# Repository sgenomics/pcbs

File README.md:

# pcbs

There are my personal PCBs... contact me for licensing information.

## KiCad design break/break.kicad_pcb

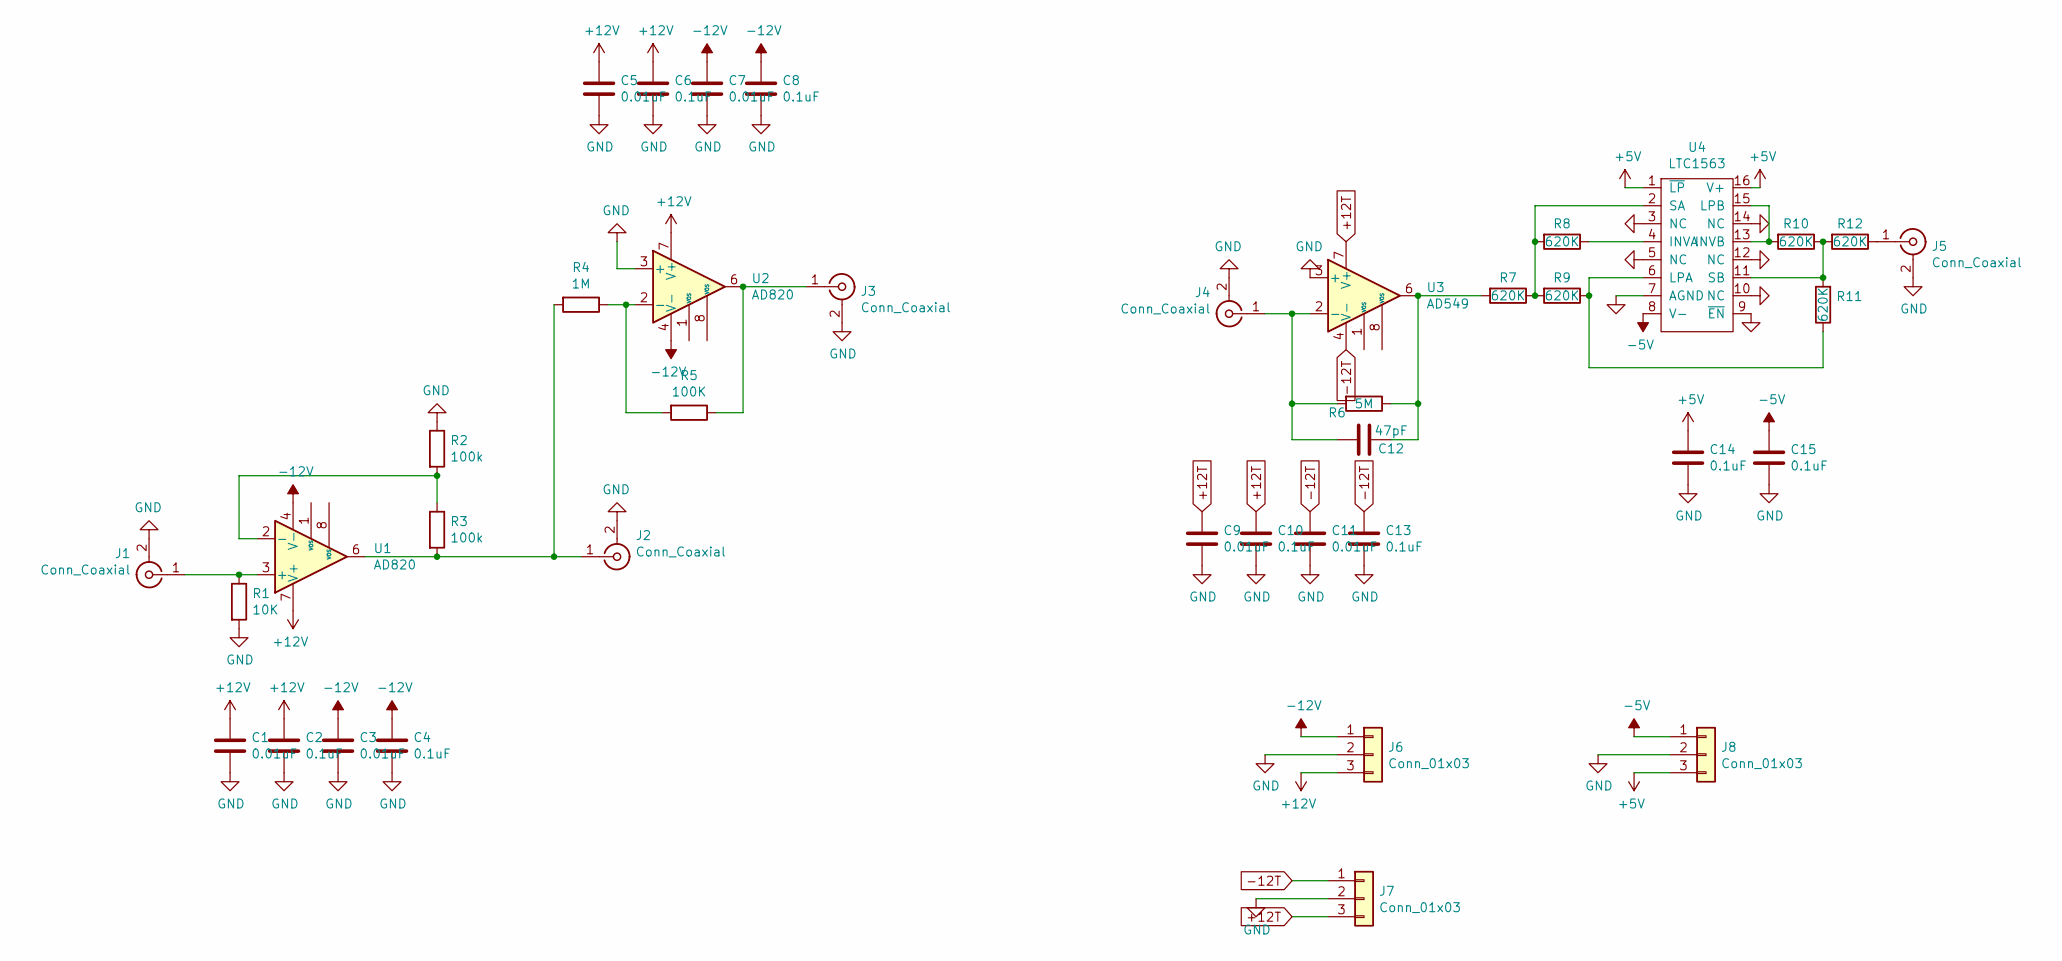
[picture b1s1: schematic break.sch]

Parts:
C1, C3, C5, C7, C9, C11: 0.01uF; C_0805_2012Metric
C2, C4, C6, C8, C10, C13, C14, C15: 0.1uF; C_0805_2012Metric
C12: 47pF; C_0805_2012Metric
J1, J2, J3, J4, J5: Conn_Coaxial; SMA_Amphenol_901-144_Vertical
J6, J7, J8: Conn_01x03; JST_EH_B3B-EH-A_1x03_P2.50mm_Vertical
R1: 10K; R_1206_3216Metric
R2, R3: 100k; R_1206_3216Metric
R4: 1M; R_1206_3216Metric
R5: 100K; R_1206_3216Metric
R6: 5M; R_1206_3216Metric
R7, R8, R9, R10, R11, R12: 620K; R_1206_3216Metric
U1, U2: AD820; SOIC-8_3.9x4.9mm_P1.27mm
U3: AD549; TO-99-8
U4: LTC1563; SSOP-16_3.9x4.9mm_P0.635mm

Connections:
+5V: C14.1, J8.3, U4.1 (~LP), U4.16 (V+)
+12T: C9.1, C10.1, J7.3, U3.7 (V+)
+12V: C1.1, C2.1, C5.1, C6.1, J6.3, U1.7 (V+), U2.7 (V+)
-5V: C15.1, J8.1, U4.8 (V-)
-12T: C11.1, C13.1, J7.1, U3.4 (V-)
-12V: C3.1, C4.1, C7.1, C8.1, J6.1, U1.4 (V-), U2.4 (V-)
GND: C1.2, C2.2, C3.2, C4.2, C5.2, C6.2, C7.2, C8.2, C9.2, C10.2, C11.2, C13.2, C14.2, C15.2, J1.2 (Ext), J2.2 (Ext), J3.2 (Ext), J4.2 (Ext), J5.2 (Ext), J6.2, J7.2, J8.2, R1.2, R2.1, U2.3 (+), U3.3 (+), U4.3 (NC), U4.5 (NC), U4.7 (AGND), U4.9 (~EN), U4.10 (NC), U4.12 (NC), U4.14 (NC)
unnamed: C12.1, R6.1, R7.2, U3.6
unnamed: C12.2, J4.1 (In), R6.2, U3.2 (-)
unnamed: J1.1 (In), R1.1, U1.3 (+)
unnamed: J2.1 (In), R3.2, R4.2, U1.6
unnamed: J3.1 (In), R5.1, U2.6
unnamed: J5.1 (In), R12.1
unnamed: R2.2, R3.1, U1.2 (-)
unnamed: R4.1, R5.2, U2.2 (-)
unnamed: R7.1, R8.2, R9.2, U4.2 (SA)
unnamed: R8.1, U4.4 (INVA)
unnamed: R10.1, R11.2, R12.2, U4.11 (SB)
unnamed: R10.2, U4.13 (INVB), U4.15 (LPB)
unnamed: R9.1, R11.1, U4.6 (LPA)

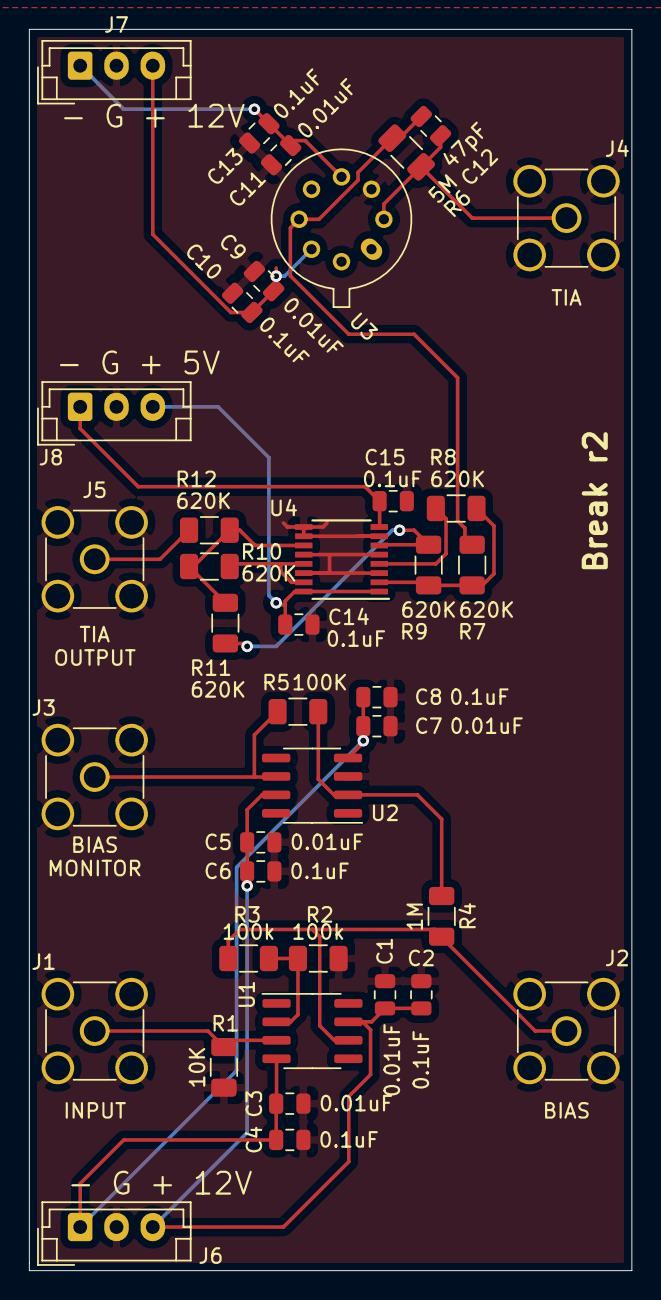
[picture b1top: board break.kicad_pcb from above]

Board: 2 copper layers, 41.5 x 85.5 mm, 39 parts (0 on the bottom side), 20 nets.

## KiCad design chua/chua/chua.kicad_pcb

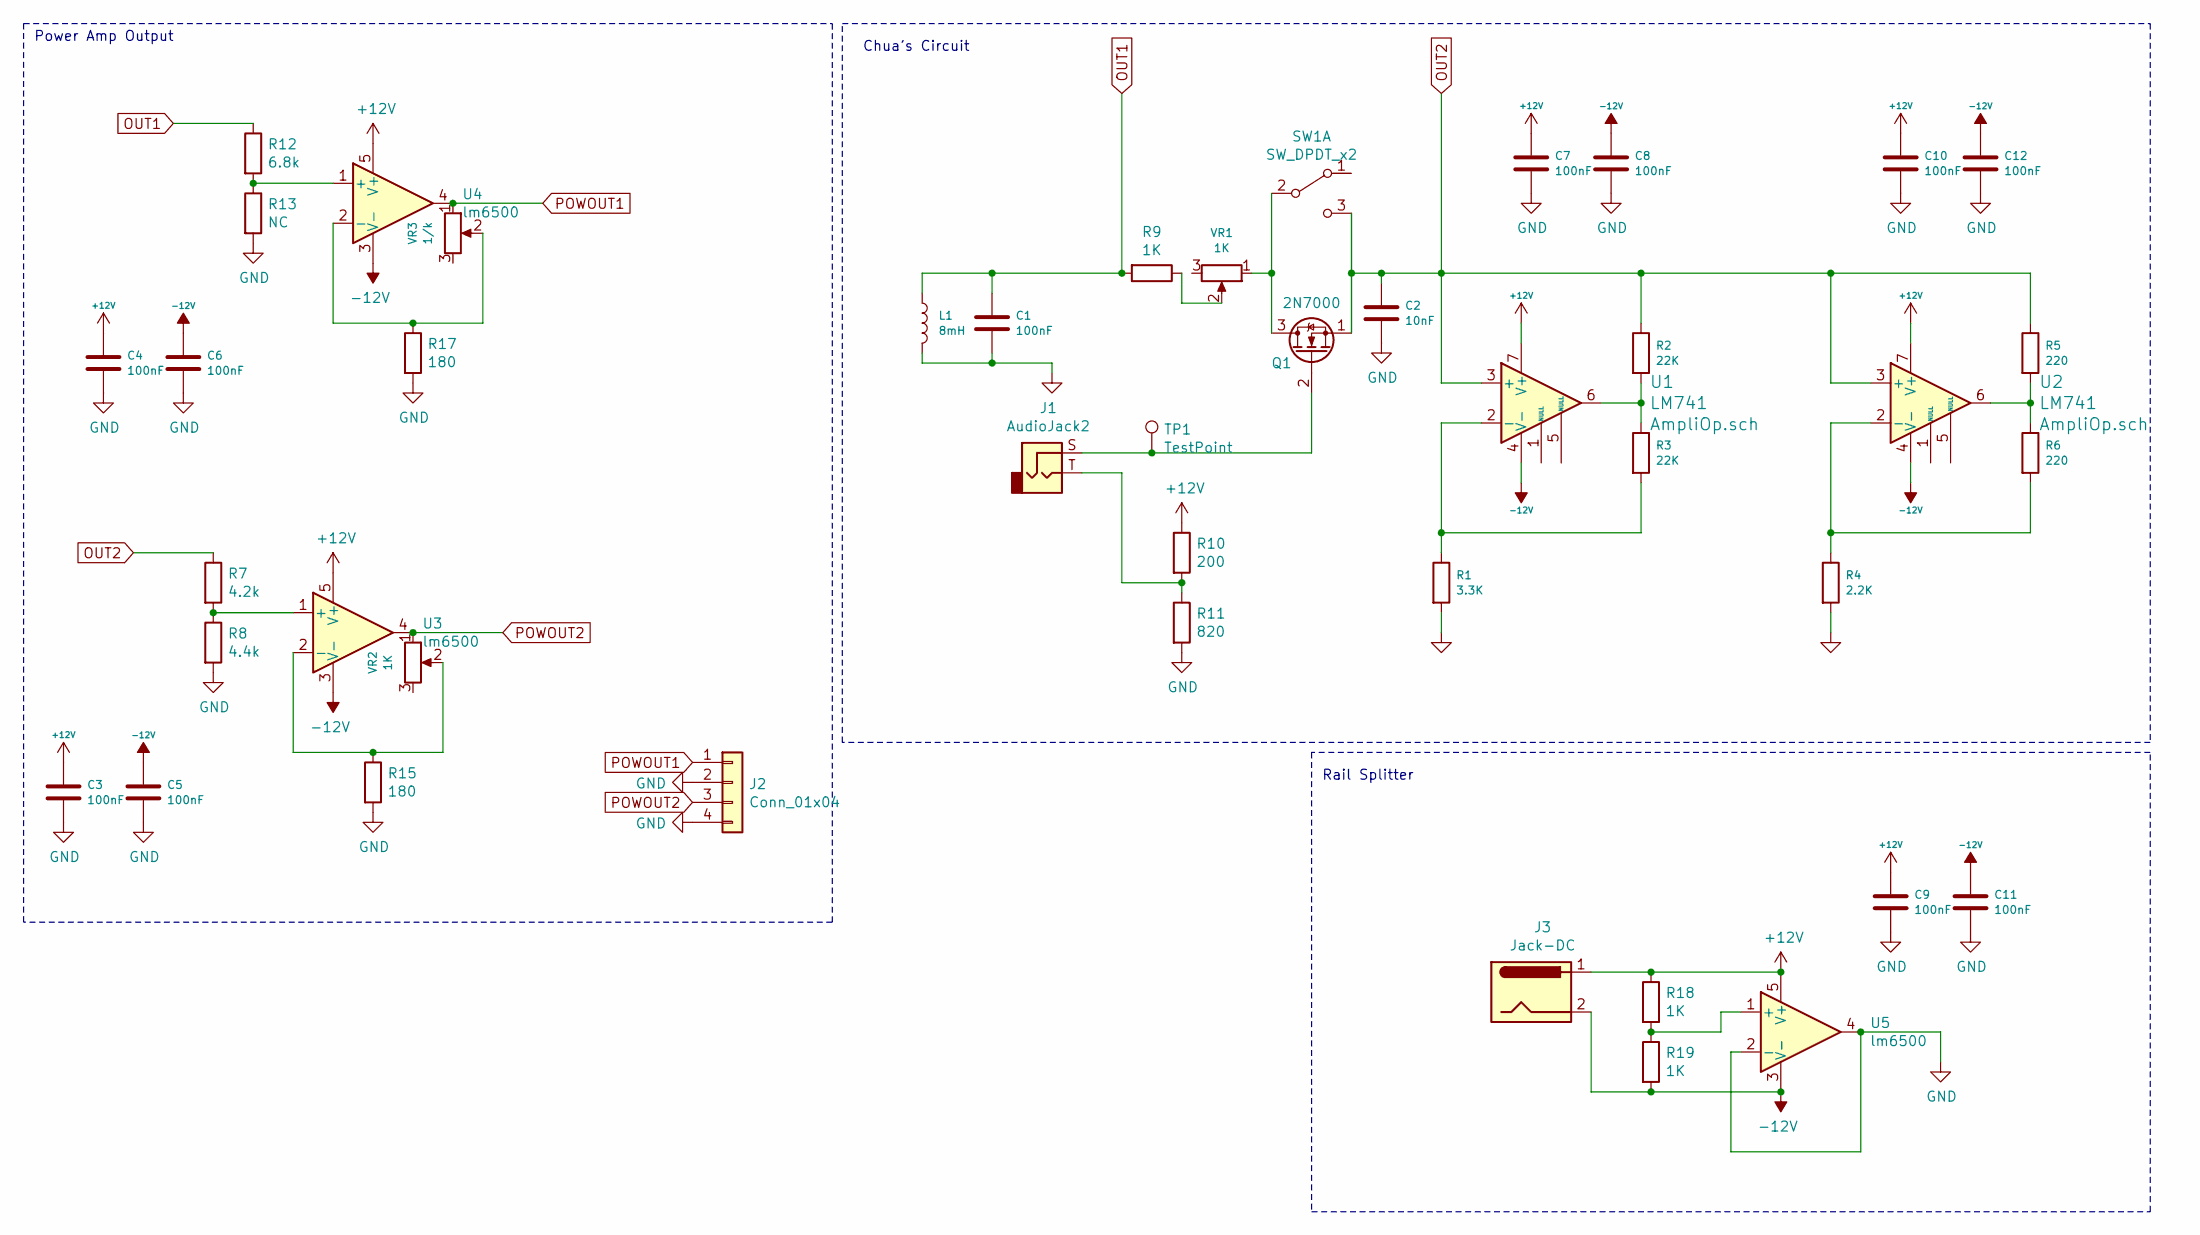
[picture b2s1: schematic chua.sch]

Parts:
C1: 100nF; C_Rect_L9.0mm_W2.5mm_P7.50mm_MKT
C2: 10nF; C_Rect_L10.0mm_W2.5mm_P7.50mm_MKS4
C3, C4, C5, C6, C7, C8, C9, C10, C11, C12: 100nF; C_Rect_L4.0mm_W2.5mm_P2.50mm
J1: AudioJack2; Banana_Jack_2Pin
J2: Conn_01x04; TerminalBlock_TE_282834-4_1x04_P2.54mm_Horizontal
J3: Jack-DC; BarrelJack_CUI_PJ-063AH_Horizontal
L1: 8mH; L_Radial_D8.7mm_P5.00mm_Fastron_07HCP
Q1: 2N7000; TO-92_Inline_Wide
R1: 3.3K; R_Axial_DIN0207_L6.3mm_D2.5mm_P10.16mm_Horizontal
R2, R3: 22K; R_Axial_DIN0207_L6.3mm_D2.5mm_P10.16mm_Horizontal
R4: 2.2K; R_Axial_DIN0207_L6.3mm_D2.5mm_P10.16mm_Horizontal
R5, R6: 220; R_Axial_DIN0207_L6.3mm_D2.5mm_P10.16mm_Horizontal
R7: 4.2k; R_Axial_DIN0207_L6.3mm_D2.5mm_P10.16mm_Horizontal
R8: 4.4k; R_Axial_DIN0207_L6.3mm_D2.5mm_P10.16mm_Horizontal
R9, R18, R19: 1K; R_Axial_DIN0207_L6.3mm_D2.5mm_P10.16mm_Horizontal
R10: 200; R_Axial_DIN0207_L6.3mm_D2.5mm_P10.16mm_Horizontal
R11: 820; R_Axial_DIN0207_L6.3mm_D2.5mm_P10.16mm_Horizontal
R12: 6.8k; R_Axial_DIN0207_L6.3mm_D2.5mm_P10.16mm_Horizontal
R13: NC; R_Axial_DIN0207_L6.3mm_D2.5mm_P10.16mm_Horizontal
R15, R17: 180; R_Axial_DIN0207_L6.3mm_D2.5mm_P10.16mm_Horizontal
SW1: SW_DPDT_x2; CK_FARN1201430
TP1: TestPoint; Test_Point_Pad_4.0x4.0mm
U1, U2: LM741; DIP-8_W7.62mm_LongPads
U3, U4, U5: lm6500; TO-220-5_P3.4x3.7mm_StaggerOdd_Lead3.8mm_Vertical
VR1, VR2: 1K; Potentiometer_WirePads_largePads
VR3: 1/k; Potentiometer_WirePads_largePads

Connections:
+12V: C3.1, C4.1, C7.1, C9.1, C10.1, J3.1, R10.1, R18.1, U1.7 (V+), U2.7 (V+), U3.5 (V+), U4.5 (V+), U5.5 (V+)
-12V: C5.1, C6.1, C8.1, C11.1, C12.1, J3.2, R19.2, U1.4 (V-), U2.4 (V-), U3.3 (V-), U4.3 (V-), U5.3 (V-)
GND: C1.2, C2.2, C3.2, C4.2, C5.2, C6.2, C7.2, C8.2, C9.2, C10.2, C11.2, C12.2, J2.2, J2.4, L1.2, R1.2, R4.2, R8.2, R11.2, R13.2, R15.2, R17.2, U5.2 (-), U5.4
unnamed: J1.S, Q1.2 (G), TP1.1
unnamed: J1.T, R10.2, R11.1
unnamed: Q1.3 (D), SW1.2 (B), VR1.1
unnamed: R1.1, R3.2, U1.2 (-)
unnamed: R2.2, R3.1, U1.6
unnamed: R4.1, R6.2, U2.2 (-)
unnamed: R5.2, R6.1, U2.6
unnamed: R7.2, R8.1, U3.1 (+)
unnamed: R9.1, VR1.2
unnamed: R12.2, R13.1, U4.1 (+)
unnamed: R15.1, U3.2 (-), VR2.2
unnamed: R17.1, U4.2 (-), VR3.2
unnamed: R18.2, R19.1, U5.1 (+)
OUT1: C1.1, L1.1, R9.2, R12.1
OUT2: C2.1, Q1.1 (S), R2.1, R5.1, R7.1, SW1.3 (C), U1.3 (+), U2.3 (+)
POWOUT1: J2.1, U4.4, VR3.1
POWOUT2: J2.3, U3.4, VR2.1

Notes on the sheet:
Chua’s Circuit
Power Amp Output
Rail Splitter

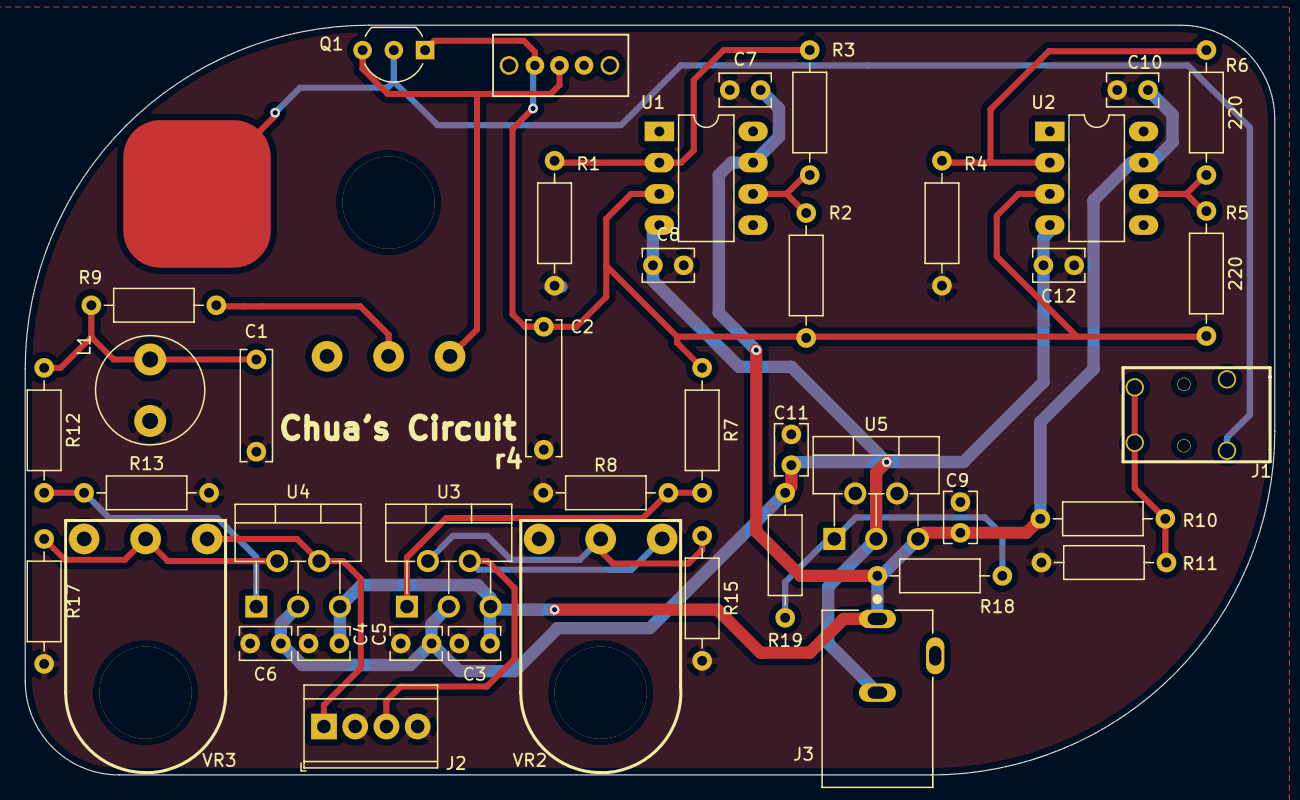
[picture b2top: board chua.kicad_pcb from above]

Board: 2 copper layers, 101.6 x 61.0 mm, 44 parts (1 on the bottom side), 20 nets.

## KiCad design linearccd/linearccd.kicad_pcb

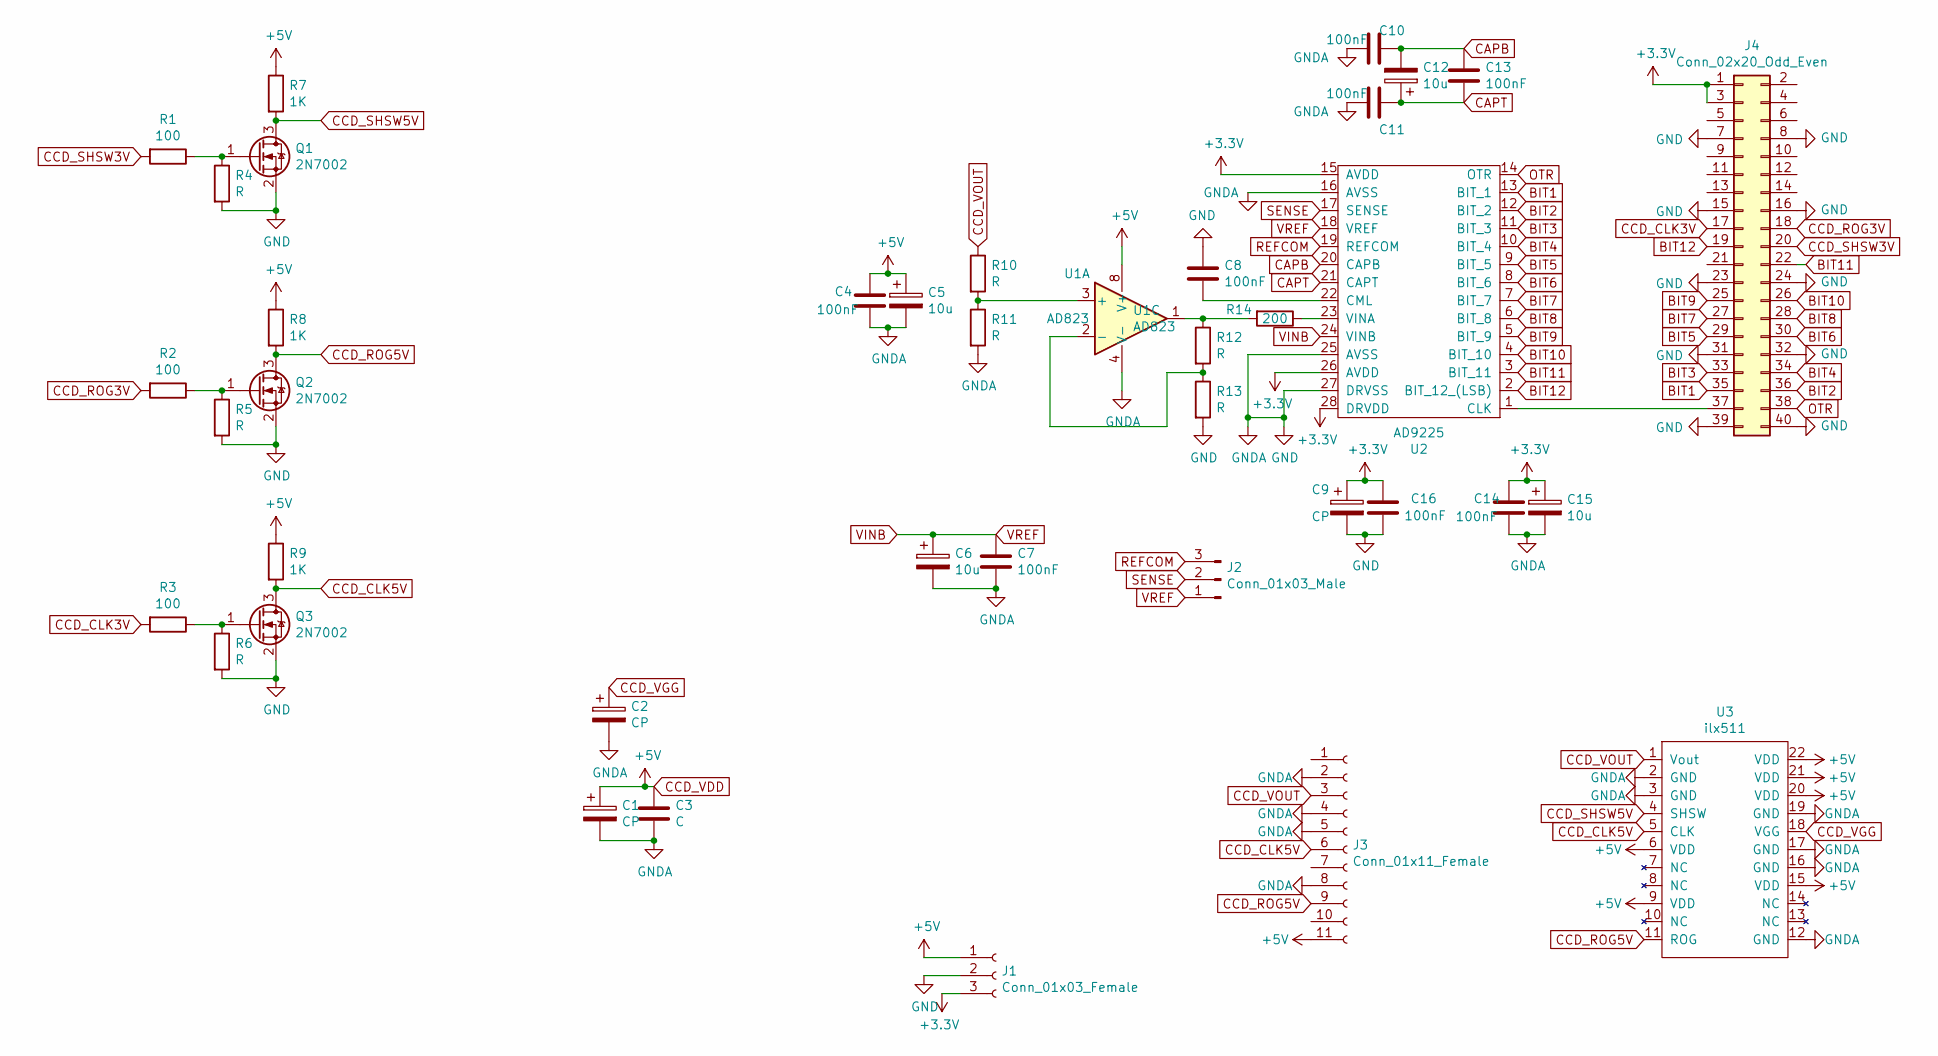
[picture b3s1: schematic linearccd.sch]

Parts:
C1, C2, C9: CP; CP_EIA-6032-15_Kemet-U_Pad2.25x2.35mm_HandSolder
C3: C; C_0805_2012Metric
C4, C7, C8, C10, C11, C13, C14, C16: 100nF; C_0805_2012Metric
C5, C6, C12, C15: 10u; CP_EIA-6032-15_Kemet-U_Pad2.25x2.35mm_HandSolder
J1: Conn_01x03_Female; PinSocket_1x03_P2.54mm_Vertical_SMD_Pin1Left
J2: Conn_01x03_Male; PinSocket_1x03_P2.54mm_Vertical_SMD_Pin1Left
J3: Conn_01x11_Female; PinSocket_1x11_P2.54mm_Vertical
J4: Conn_02x20_Odd_Even; PinSocket_2x20_P2.54mm_Vertical_SMD
Q1, Q2, Q3: 2N7002; SOT-23
R1, R2, R3: 100; C_0805_2012Metric
R4, R5, R6, R10, R11, R12, R13: R; C_0805_2012Metric
R7, R8, R9: 1K; C_0805_2012Metric
R14: 200; C_0805_2012Metric
U1: AD823; SOIC-8_3.9x4.9mm_P1.27mm
U2: AD9225; SOIC-28W_7.5x18.7mm_P1.27mm
U3: ilx511; DIP-22_W10.16mm_LongPads

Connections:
+3V3: C9.1, C14.1, C15.1, C16.1, J1.3, J4.1, J4.3, U2.15 (AVDD), U2.26 (AVDD), U2.28 (DRVDD)
BIT1: J4.35, U2.13 (BIT_1)
BIT2: J4.36, U2.12 (BIT_2)
BIT3: J4.33, U2.11 (BIT_3)
BIT4: J4.34, U2.10 (BIT_4)
BIT5: J4.29, U2.9 (BIT_5)
BIT6: J4.30, U2.8 (BIT_6)
BIT7: J4.27, U2.7 (BIT_7)
BIT8: J4.28, U2.6 (BIT_8)
BIT9: J4.25, U2.5 (BIT_9)
BIT10: J4.26, U2.4 (BIT_10)
BIT11: J4.22, U2.3 (BIT_11)
BIT12: J4.19, U2.2 (BIT_12_(LSB))
CAPB: C10.1, C12.2, C13.1, U2.20 (CAPB)
CAPT: C11.1, C12.1, C13.2, U2.21 (CAPT)
CCD_CLK3V: J4.17, R3.2
CCD_CLK5V: J3.6, Q3.3 (D), R9.2, U3.5 (CLK)
CCD_ROG3V: J4.18, R2.2
CCD_ROG5V: J3.9, Q2.3 (D), R8.2, U3.11 (ROG)
CCD_SHSW3V: J4.20, R1.2
CCD_SHSW5V: Q1.3 (D), R7.2, U3.4 (SHSW)
CCD_VDD: C1.1, C3.1, C4.1, C5.1, J1.1, J3.11, R7.1, R8.1, R9.1, U1.8 (V+), U3.6 (VDD), U3.9 (VDD), U3.15 (VDD), U3.20 (VDD), U3.21 (VDD), U3.22 (VDD)
CCD_VGG: C2.1, U3.18 (VGG)
CCD_VOUT: J3.3, R10.1, U3.1 (Vout)
GND: C1.2, C2.2, C3.2, C4.2, C5.2, C6.2, C7.2, C8.1, C9.2, C10.2, C11.2, C14.2, C15.2, C16.2, J1.2, J3.2, J3.4, J3.5, J3.8, J4.7, J4.8, J4.15, J4.16, J4.23, J4.24, J4.31, J4.32, J4.39, J4.40, Q1.2 (S), Q2.2 (S), Q3.2 (S), R4.2, R5.2, R6.2, R11.2, R13.2, U1.4 (V-), U2.16 (AVSS), U2.25 (AVSS), U2.27 (DRVSS), U3.2 (GND), U3.3 (GND), U3.12 (GND), U3.16 (GND), U3.17 (GND), U3.19 (GND)
unnamed: C8.2, U2.22 (CML)
unnamed: J4.37, U2.1 (CLK)
unnamed: Q1.1 (G), R1.1, R4.1
unnamed: Q2.1 (G), R2.1, R5.1
unnamed: Q3.1 (G), R3.1, R6.1
unnamed: R10.2, R11.1, U1.3 (+)
unnamed: R12.1, R14.2, U1.1
unnamed: R12.2, R13.1, U1.2 (-)
unnamed: R14.1, U2.23 (VINA)
OTR: J4.38, U2.14 (OTR)
REFCOM: J2.3, U2.19 (REFCOM)
SENSE: J2.2, U2.17 (SENSE)
VINB: C6.1, C7.1, J2.1, U2.18 (VREF), U2.24 (VINB)

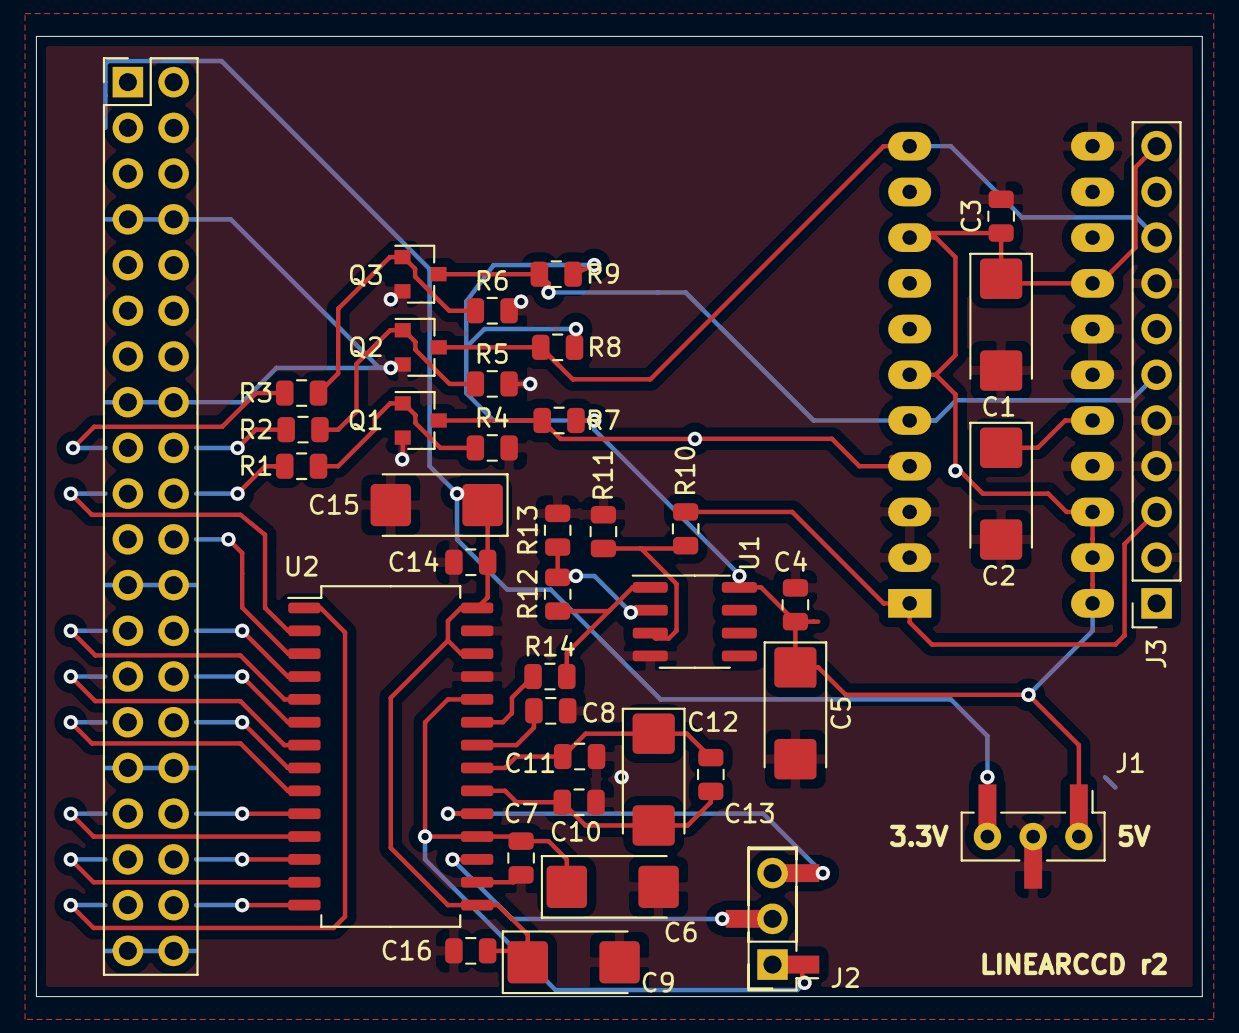
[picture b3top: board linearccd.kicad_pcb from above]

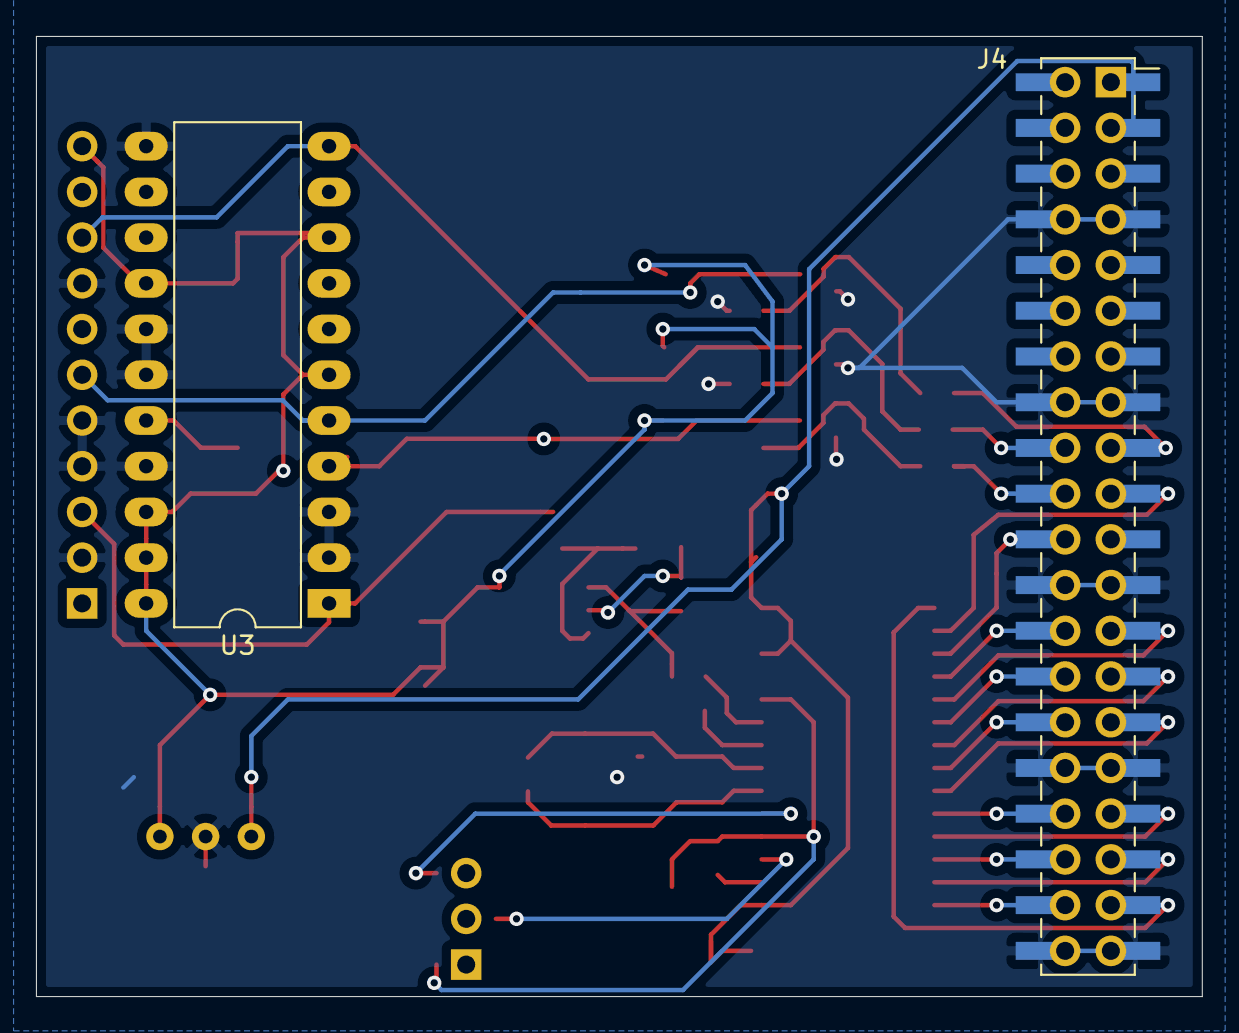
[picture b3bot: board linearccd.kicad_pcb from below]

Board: 2 copper layers, 64.8 x 53.3 mm, 40 parts (2 on the bottom side), 38 nets.

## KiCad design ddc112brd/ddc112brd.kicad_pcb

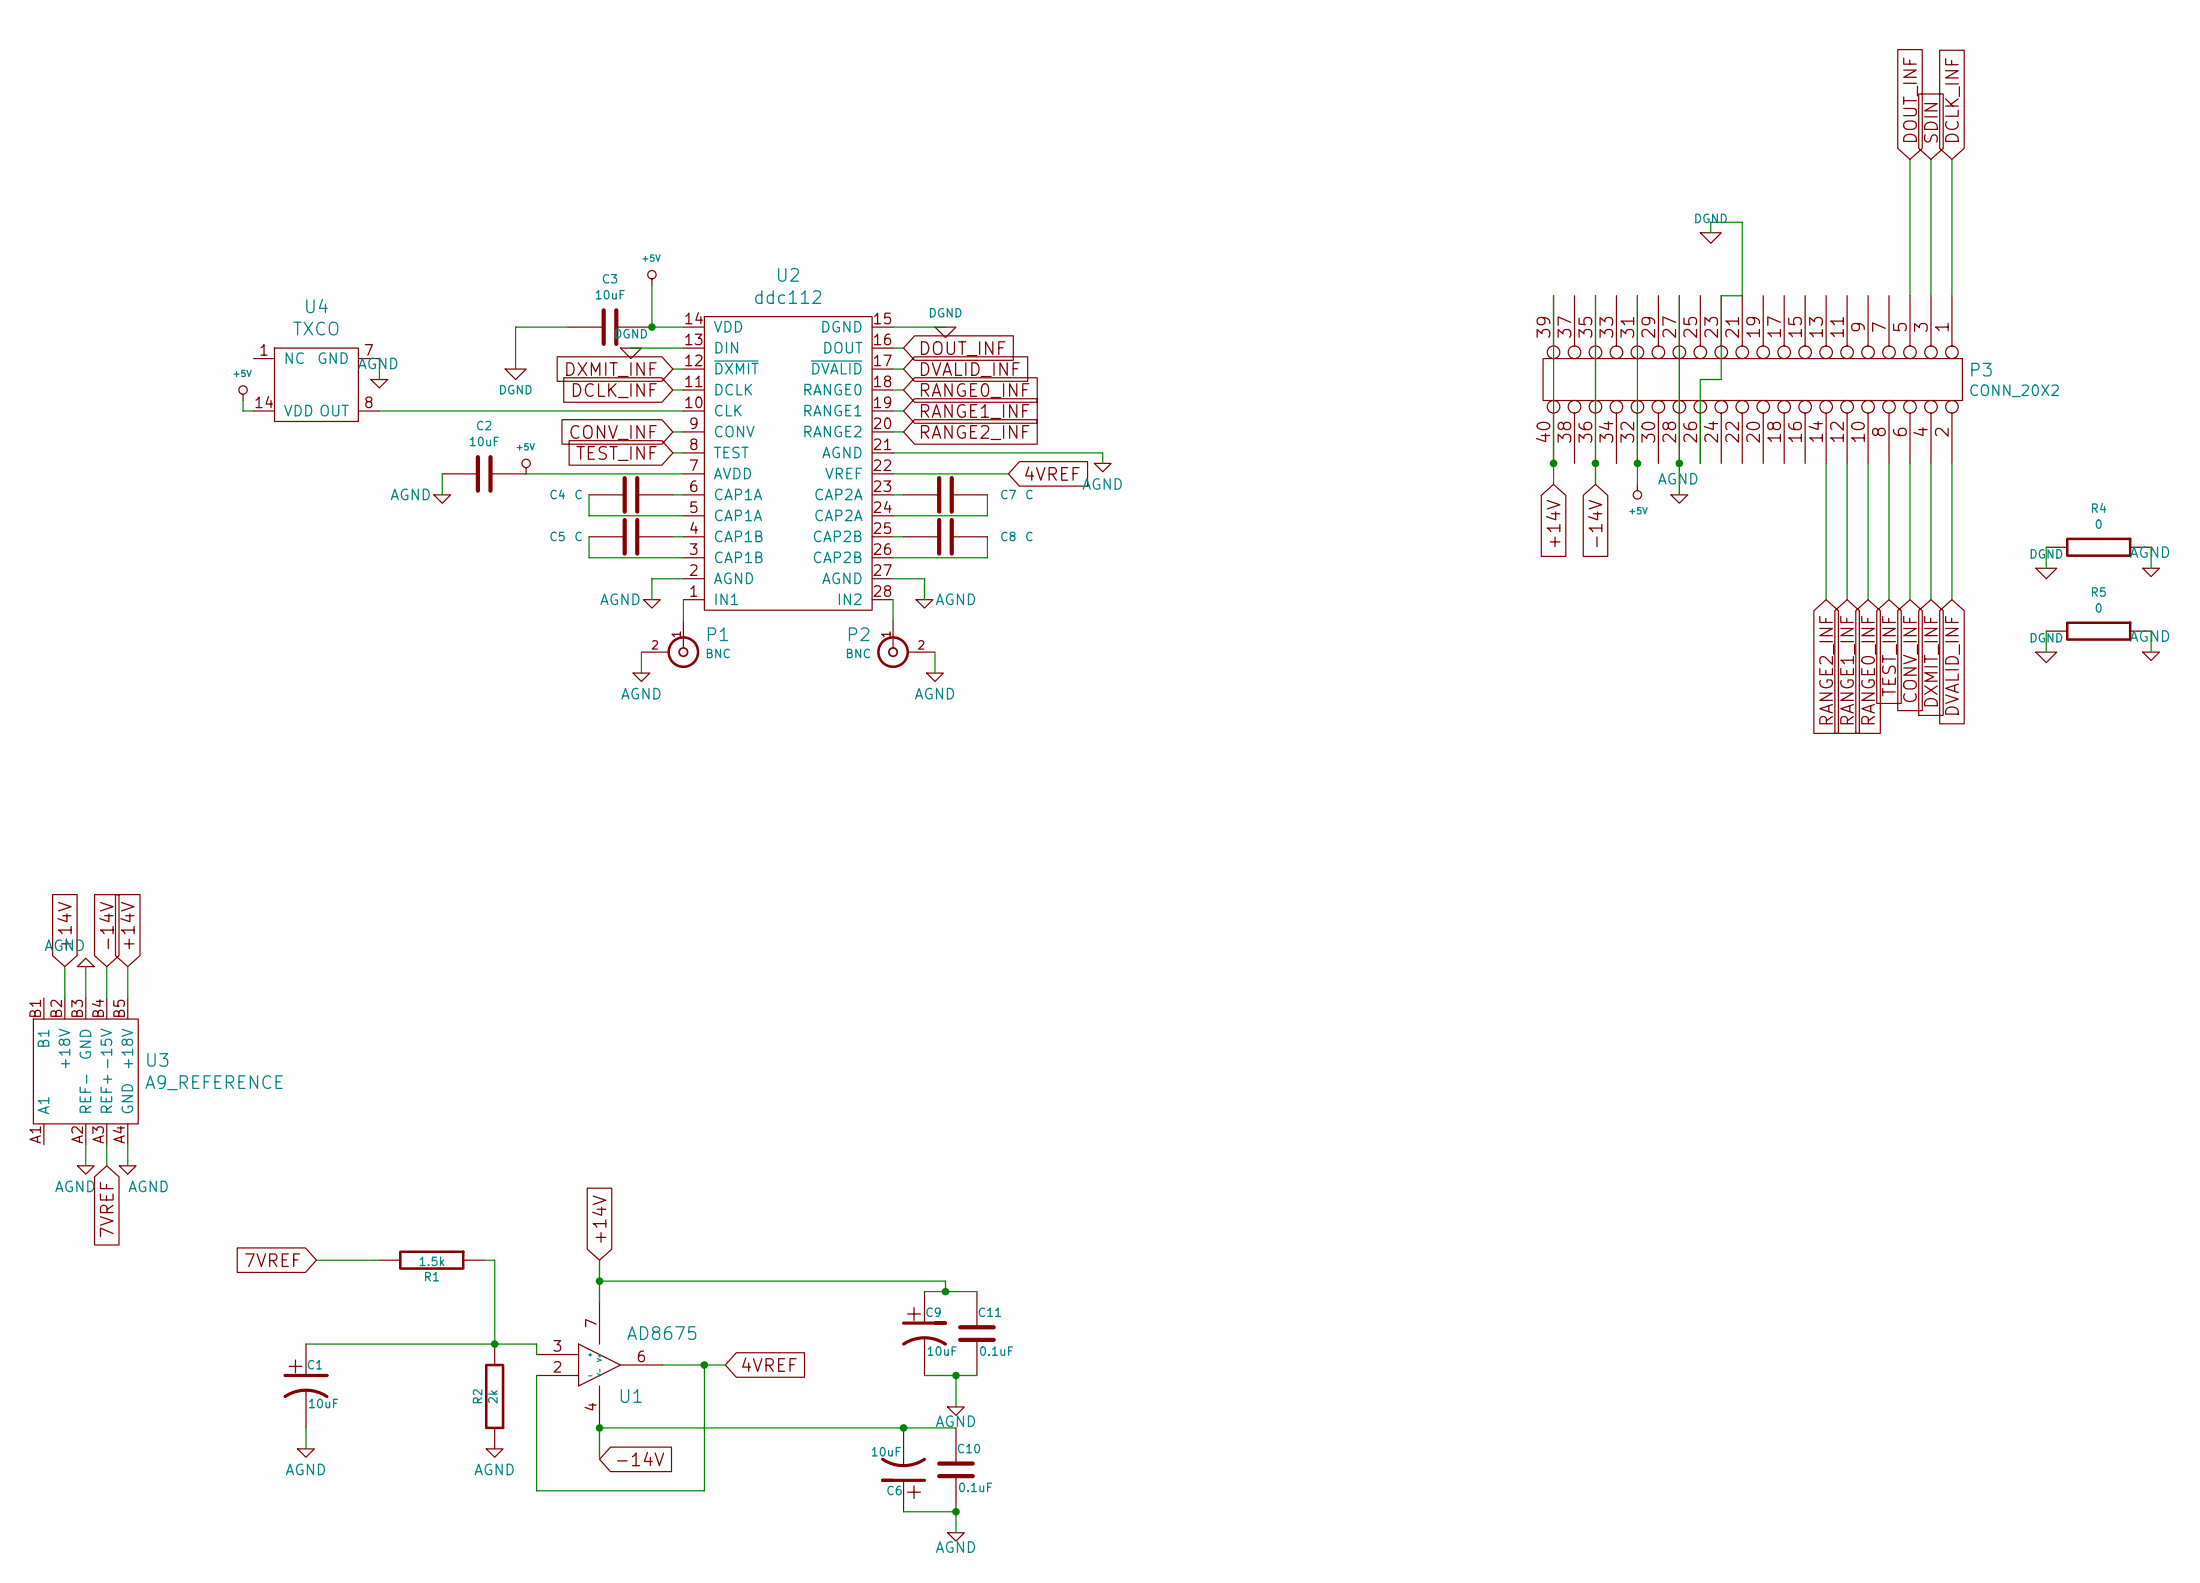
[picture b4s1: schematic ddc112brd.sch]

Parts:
C1, C2, C3, C6, C9: 10uF; SMD-1210_Pol
C4, C5, C7, C8: C; C_1206_HandSoldering
C10, C11: 0.1uF; C_0805_HandSoldering
P1, P2: BNC; SMA
P3: CONN_20X2; IDC-Header_2x20_Pitch2.54mm_Straight
R1: 1.5k; R_0805_HandSoldering
R2: 2k; R_0805_HandSoldering
R4, R5: 0; R_0201_NoSilk
U1: AD8675; SOIC-8_3.9x4.9mm_Pitch1.27mm
U2: ddc112; SOIC-28W_7.5x17.9mm_Pitch1.27mm
U3: A9_REFERENCE; A9REFERENCE
U4: TXCO

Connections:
4VREF: U1.2 (-), U1.6, U2.22 (VREF)
7VREF: R1.2, U3.A3 (REF+)
+5V: C2.1, C3.1, P3.31, P3.32, U2.7 (AVDD), U2.14 (VDD), U4.14 (VDD)
+14V: C9.1, C11.1, P3.39, P3.40, U1.7 (V+), U3.B2 (+18V), U3.B5 (+18V)
-14V: C6.2, C10.1, P3.35, P3.36, U1.4 (V-), U3.B4 (-15V)
AGND: C1.2, C2.2, C6.1, C9.2, C10.2, C11.2, P1.2 (Ext), P2.2 (Ext), P3.27, P3.28, R2.1, R4.1, R5.1, U2.2 (AGND), U2.21 (AGND), U2.27 (AGND), U3.A2 (REF-), U3.A4 (GND), U3.B3 (GND), U4.7 (GND)
CONV_INF: P3.6, U2.9 (CONV)
DCLK_INF: P3.1, U2.11 (DCLK)
DGND: C3.2, P3.21, P3.23, P3.26, R4.2, R5.2, U2.13 (DIN), U2.15 (DGND)
DOUT_INF: P3.5, U2.16 (DOUT)
DVALID_INF: P3.2, U2.17 (~DVALID)
DXMIT_INF: P3.4, U2.12 (~DXMIT)
unnamed: C1.1, R1.1, R2.2, U1.3 (+)
unnamed: C4.1, U2.6 (CAP1A)
unnamed: C4.2, U2.5 (CAP1A)
unnamed: C5.1, U2.4 (CAP1B)
unnamed: C5.2, U2.3 (CAP1B)
unnamed: C7.1, U2.24 (CAP2A)
unnamed: C7.2, U2.23 (CAP2A)
unnamed: C8.1, U2.26 (CAP2B)
unnamed: C8.2, U2.25 (CAP2B)
unnamed: P1.1 (In), U2.1 (IN1)
unnamed: P2.1 (In), U2.28 (IN2)
unnamed: U2.10 (CLK), U4.8 (OUT)
RANGE0_INF: P3.10, U2.18 (RANGE0)
RANGE1_INF: P3.12, U2.19 (RANGE1)
RANGE2_INF: P3.14, U2.20 (RANGE2)
SDIN: P3.3
TEST_INF: P3.8, U2.8 (TEST)

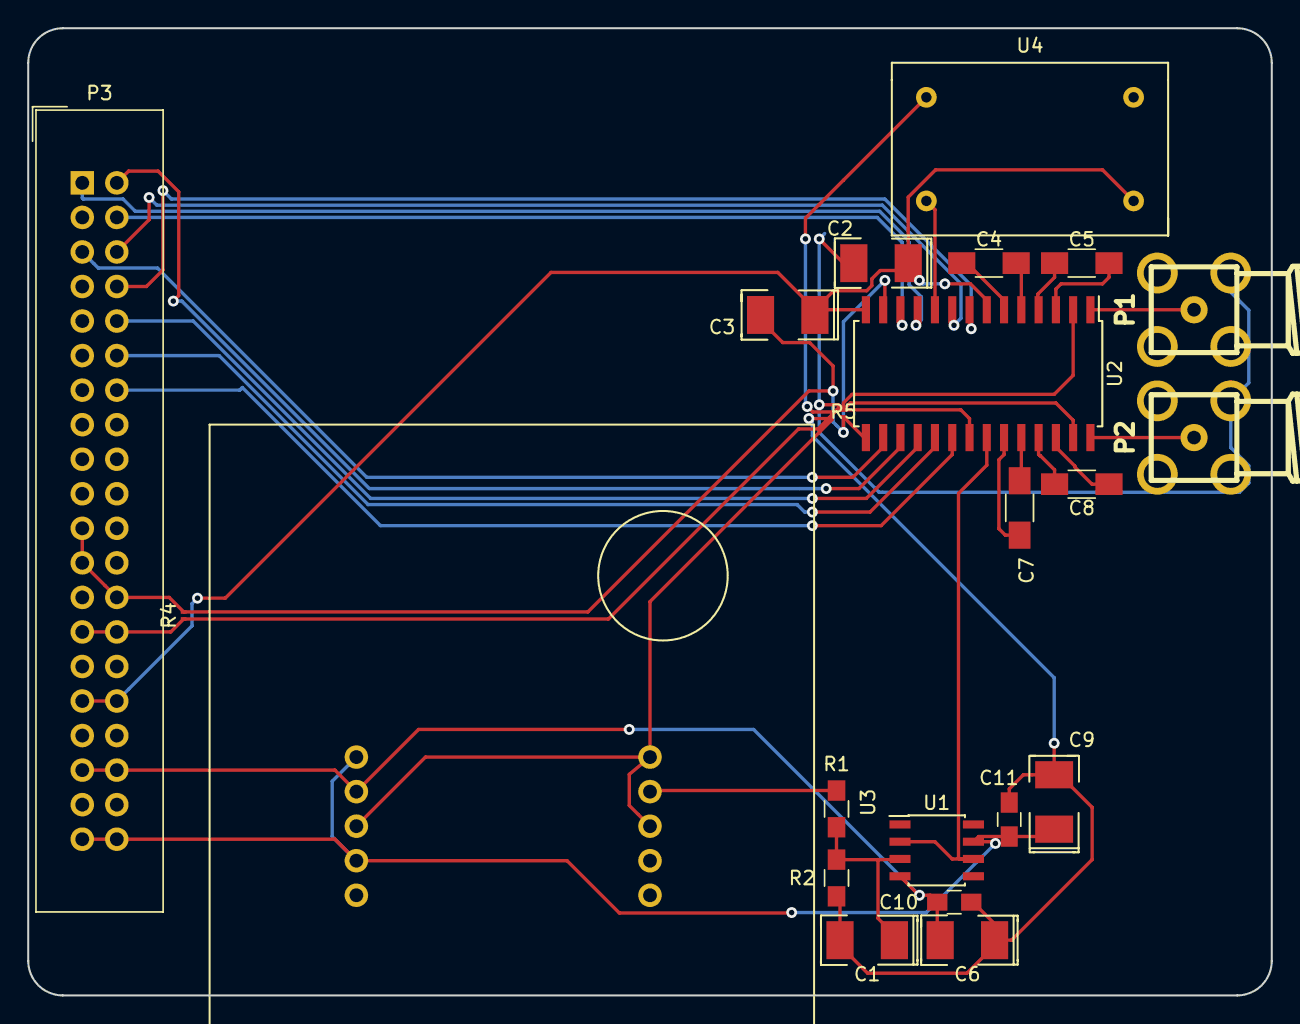
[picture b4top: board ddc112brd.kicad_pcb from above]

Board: 2 copper layers, 91.4 x 71.1 mm, 22 parts (0 on the bottom side), 28 nets.

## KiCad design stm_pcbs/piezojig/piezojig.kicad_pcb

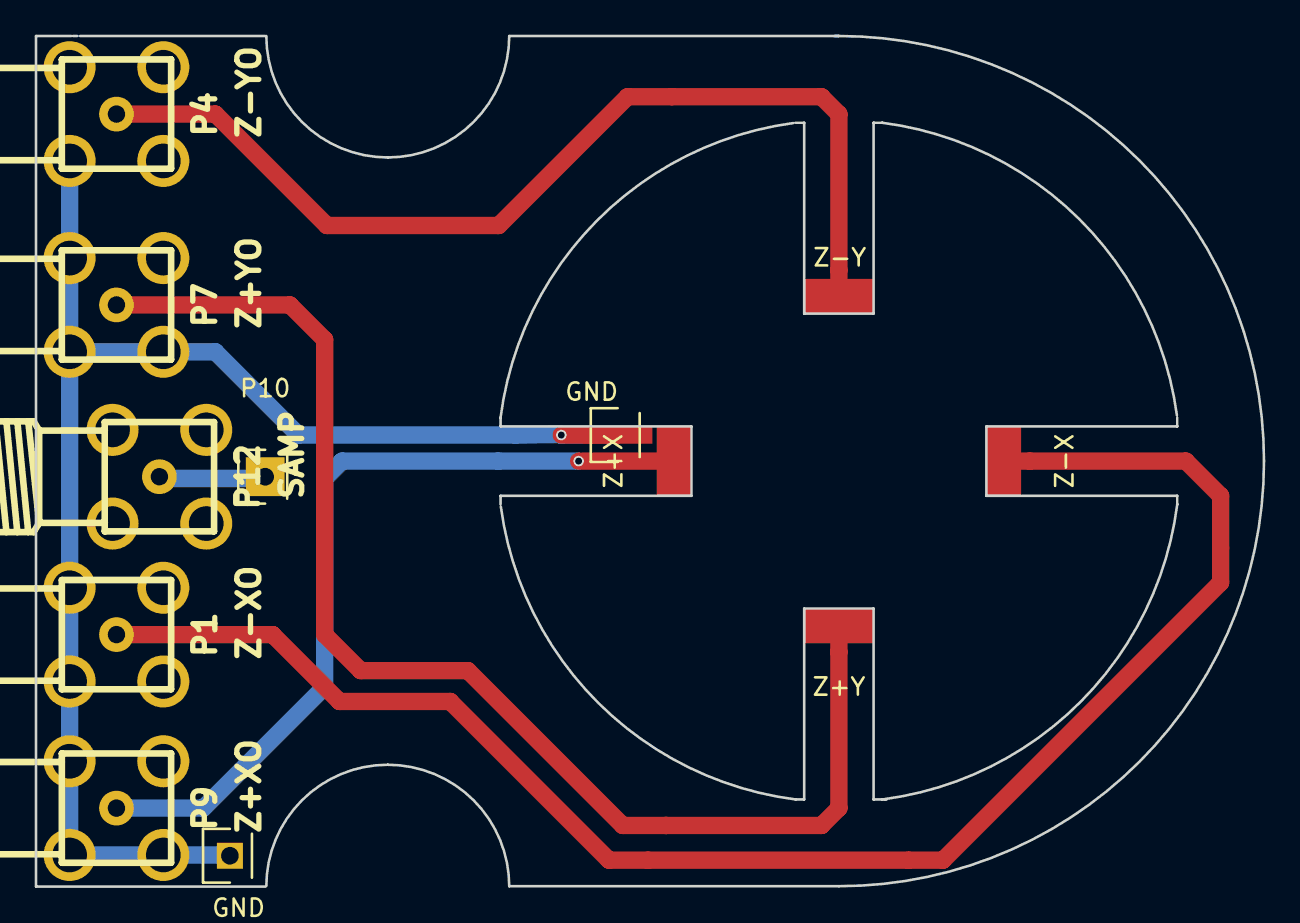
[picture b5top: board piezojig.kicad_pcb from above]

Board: 2 copper layers, 70.8 x 49.0 mm, 13 parts (1 on the bottom side), 6 nets.

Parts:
P1: Z-XO; SMA
P2: Z-X; piezopad
P4: Z-YO; SMA
P5: Z-Y; piezopad
P6: Z+Y; piezopad
P7: Z+YO; SMA
P8: Z+X; piezopad
P9: Z+XO; SMA
P10: SAMP; Socket_Strip_Straight_1x01
P11, P13, P13#2: GND; Socket_Strip_Straight_1x01
P12: SAMP; SMA

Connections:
GND: P1.2, P7.2, P9.2, P11.1, P13.1, P13#2.1
unnamed: P1.1, P2.1
unnamed: P4.1, P5.1
unnamed: P6.1, P7.1
unnamed: P8.1, P9.1
unnamed: P10.1, P12.1
